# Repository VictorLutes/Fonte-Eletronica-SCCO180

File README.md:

# Fonte-Eletrônica-SCCO180
simulação no falstad: http://tinyurl.com/ya4fsfwo
Vídeo: https://youtu.be/-Apqu-qhNC8
Lista de componentes: https://docs.google.com/document/d/1Lj97tok6SyIvny0IKN7p0XYSt3JMEMqwQmHhLOwqQxM/edit?usp=sharing

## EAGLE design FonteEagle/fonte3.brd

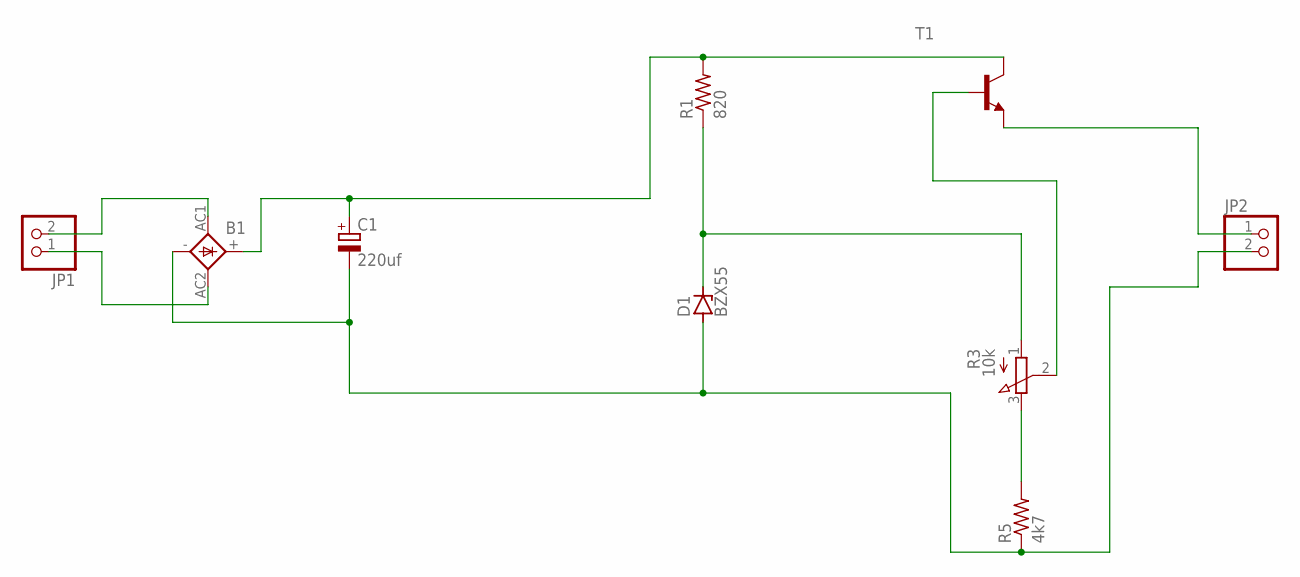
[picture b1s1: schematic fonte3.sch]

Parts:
B1: 1KAB
C1: 220uf; E5-10,5
D1: BZX55; DO35Z10
JP1, JP2: PINHD-1X2; 1X02
R1: 820; 0309/12
R3: 10k; 3RP/1610N
R5: 4k7; 0309/12
T1: -NPN-TO5; TO5

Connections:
unnamed: B1.AC1, JP1.2
unnamed: B1.AC2, JP1.1
unnamed: B1.+, C1.+, R1.2, T1.3 (C)
unnamed: R3.3 (E), R5.2
unnamed: B1.-, C1.-, D1.A, JP2.2, R5.1
unnamed: JP2.1, T1.1 (E)
unnamed: R3.2 (S), T1.2 (B)
unnamed: D1.C, R1.1, R3.1 (A)

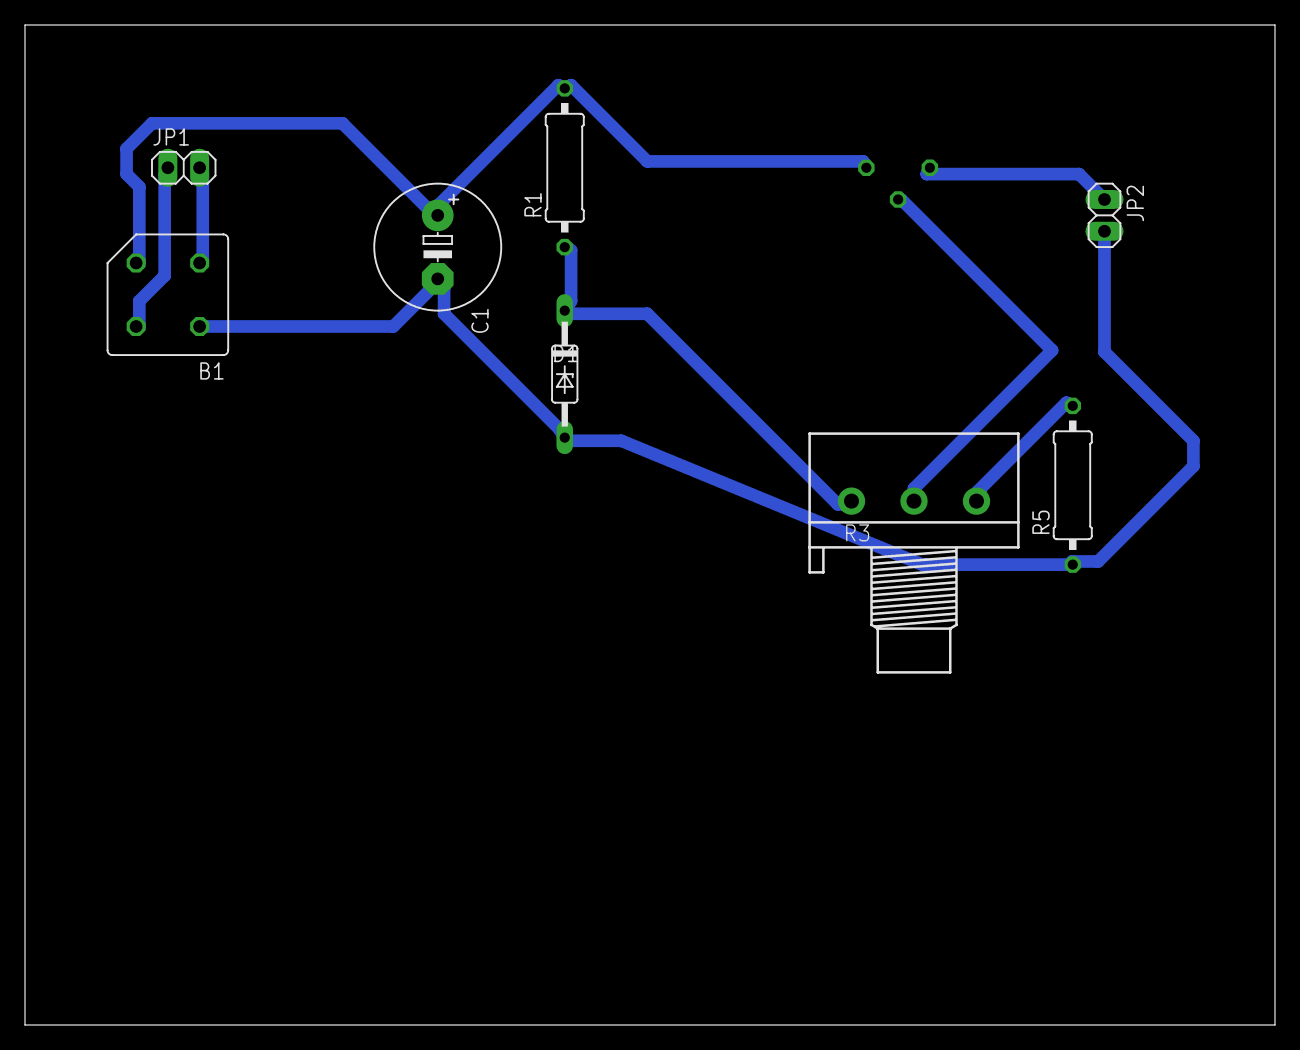
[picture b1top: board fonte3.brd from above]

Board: 2 copper layers, 100.0 x 80.0 mm, 9 parts (1 on the bottom side), 8 nets.
